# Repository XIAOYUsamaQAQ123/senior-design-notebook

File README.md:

# Senior Design Notebook

This repository serves as a **digital lab notebook** for Liangcheng's Senior Design project.

## 📂 Structure
- **docs/** → Project documentation
- **experiments/** → Experimental results.
- **src/** → Source code for the project.
- **hardware/** → PCB designs, schematics, and CAD files.
- **reports/** → Proposal, presentation, and final reports.

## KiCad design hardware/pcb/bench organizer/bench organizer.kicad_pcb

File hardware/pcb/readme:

# PCB Designs

This folder contains all the PCB design files used throughout our project. 
It includes schematics, layout files, and fabrication outputs for each board revision.

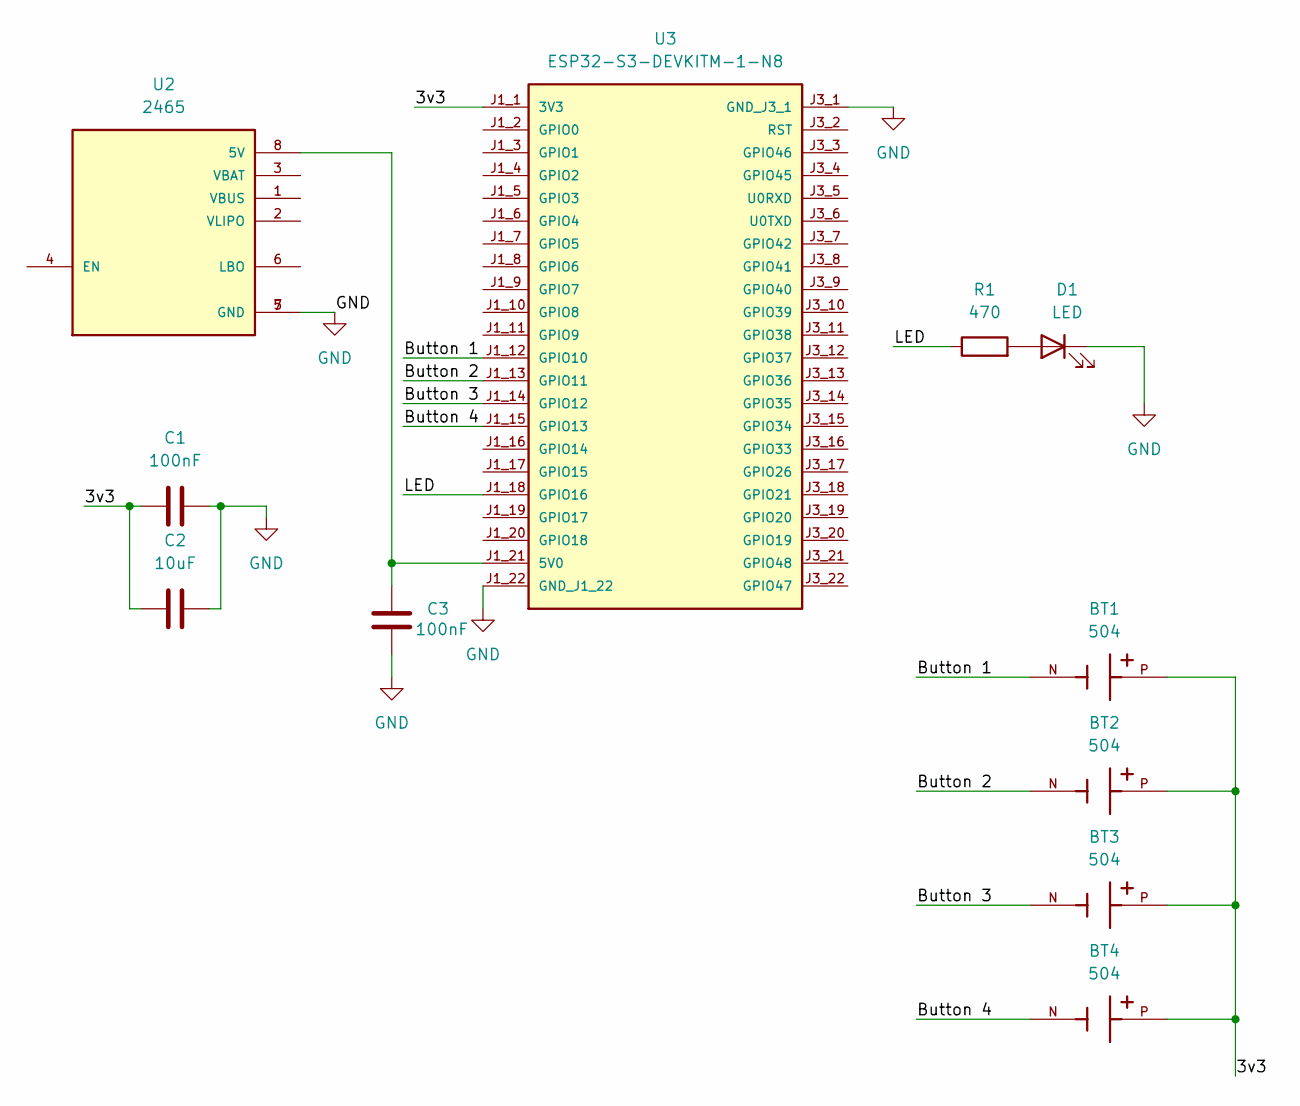
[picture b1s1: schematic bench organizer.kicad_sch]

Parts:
BT1, BT2, BT3, BT4: 504; BAT_504; PARTREV H
C1, C3: 100nF; CP_Radial_D5.0mm_P2.50mm
C2: 10uF; CP_Radial_D5.0mm_P2.50mm
D1: LED; LED_D5.0mm
R1: 470; R_Axial_DIN0207_L6.3mm_D2.5mm_P7.62mm_Horizontal
U2: 2465; MODULE_2465; PARTREV B
U3: ESP32-S3-DEVKITM-1-N8; MODULE_ESP32-S3-DEVKITM-1-N8; PARTREV 1.0

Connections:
/3v3: BT1.P, BT2.P, BT3.P, BT4.P, C1.1, C2.1, U3.J1_1 (3V3)
/Button 1: BT1.N, U3.J1_12 (GPIO10)
/Button 2: BT2.N, U3.J1_13 (GPIO11)
/Button 3: BT3.N, U3.J1_14 (GPIO12)
/Button 4: BT4.N, U3.J1_15 (GPIO13)
/LED: R1.1, U3.J1_18 (GPIO16)
GND: C1.2, C2.2, C3.2, D1.1 (K), U2.5 (GND), U2.7 (GND), U3.J1_22 (GND_J1_22), U3.J3_1 (GND_J3_1)
unnamed: D1.2 (A), R1.2
unnamed: C3.1, U2.8 (5V), U3.J1_21 (5V0)

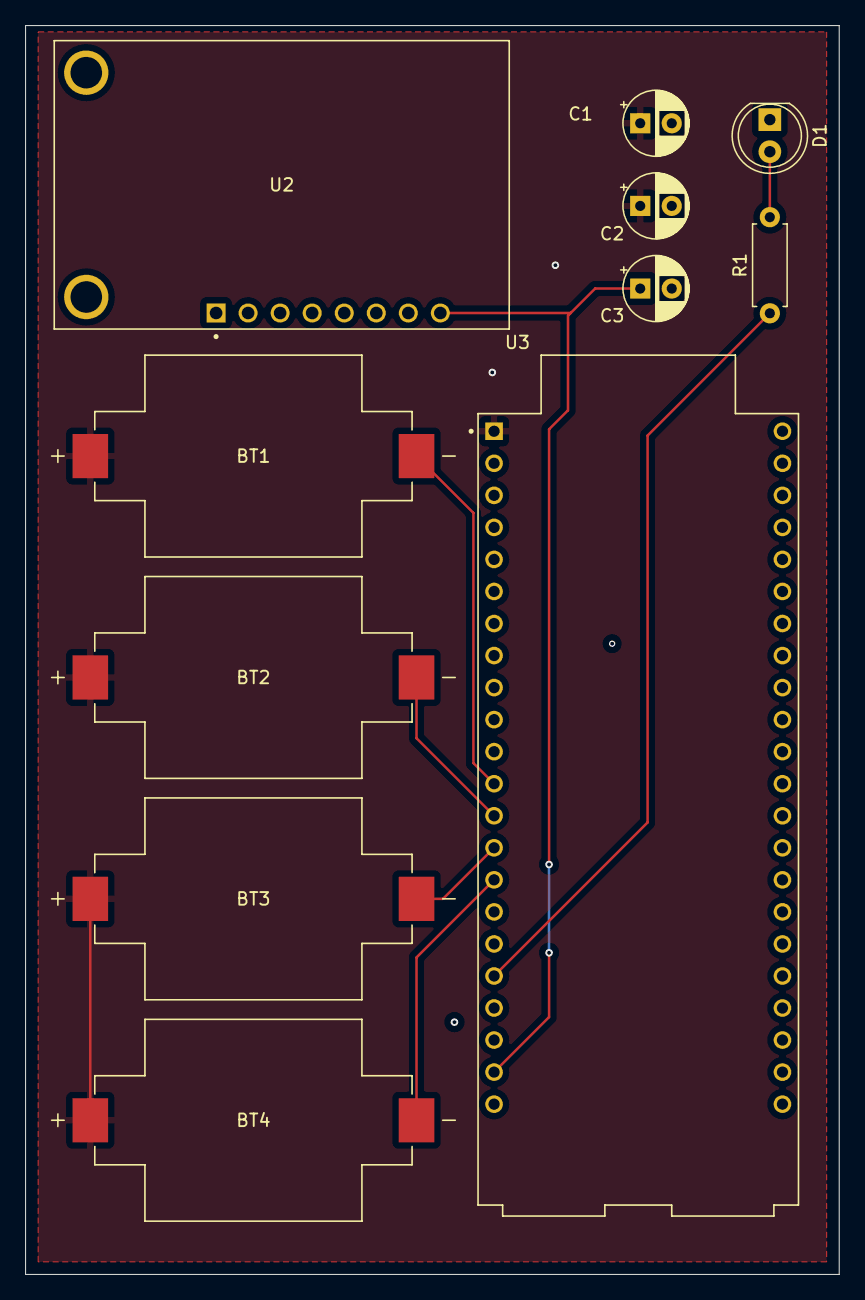
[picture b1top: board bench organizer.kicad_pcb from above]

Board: 2 copper layers, 64.5 x 99.0 mm, 11 parts (0 on the bottom side), 9 nets.

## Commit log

2025-05-07 Add files via upload
    add proposal
2025-05-07 testing code
2025-05-07 breadboard demo code
2025-05-07 presentation
2025-05-07 old design/schematic(no longer used)
2025-05-07 pcb design/schematic
2025-05-07 extra cost
2025-05-08 Liangcheng Sun's worklog here
2025-05-08 Liangcheng's worklog here
2025-05-08 Liangcheng's file
2025-05-08 Liangcheng's worklog
